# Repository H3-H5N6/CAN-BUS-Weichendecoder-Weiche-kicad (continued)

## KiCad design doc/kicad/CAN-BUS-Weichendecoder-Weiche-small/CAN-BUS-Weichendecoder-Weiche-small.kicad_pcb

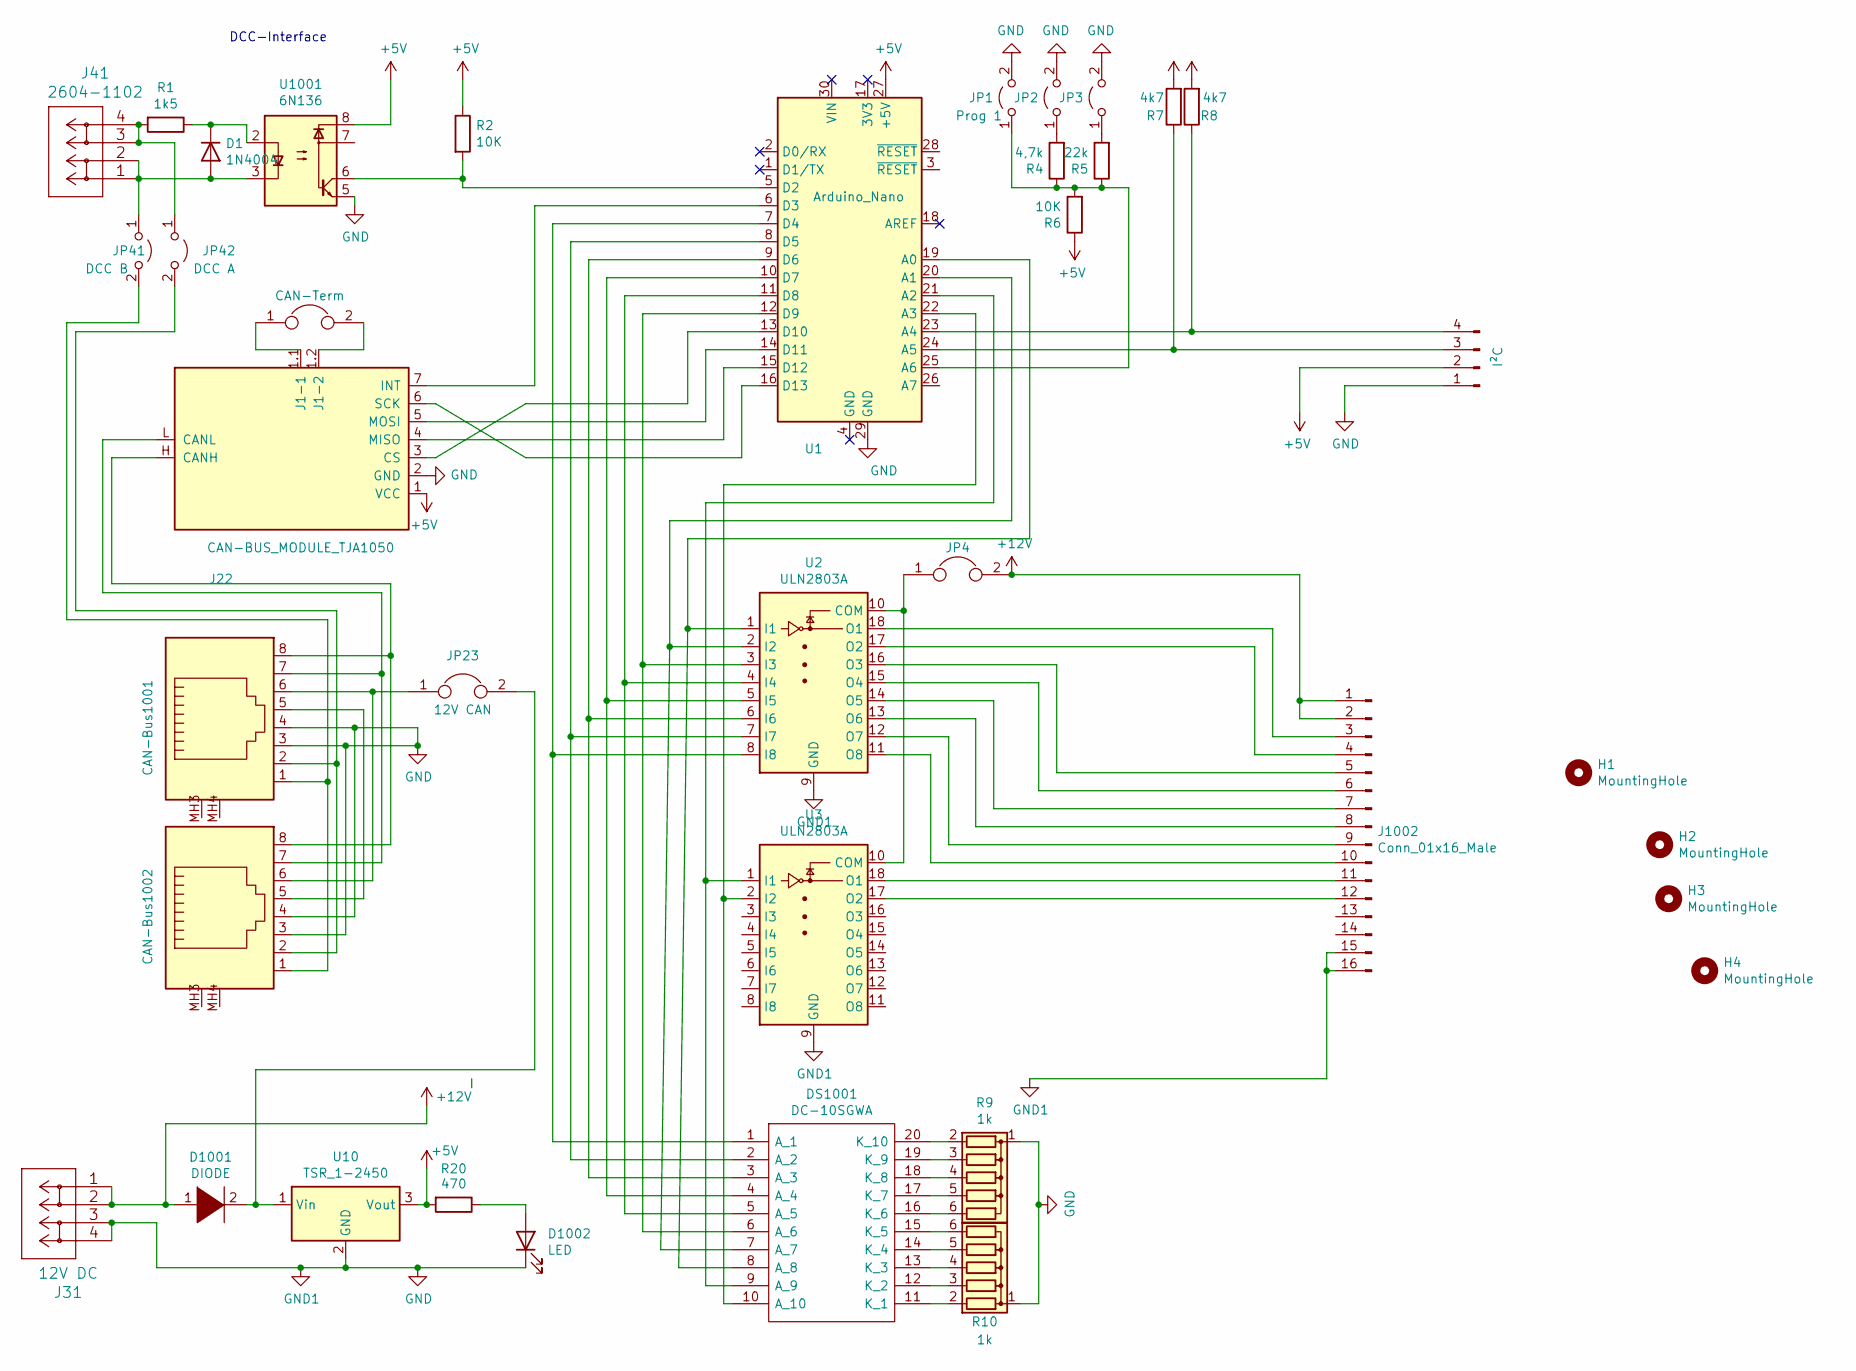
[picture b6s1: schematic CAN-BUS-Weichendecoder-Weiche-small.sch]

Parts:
CAN-Bus1001, CAN-Bus1002: J22; A20042LPFS
D1: 1N4004; D_DO-15_P10.16mm_Horizontal
D1001: DIODE; D_DO-15_P10.16mm_Horizontal
D1002: LED; LED_D3.0mm
DS1001: DC-10SGWA; DIPS750W80P254L2540H825Q20N; Manufacturer_Part_Number DC-10SGWA; Mouser Part Number N/A
H1, H2, H3, H4: MountingHole; MountingHole_3.2mm_M3
J31: 12V DC; CONN_2604-1102_4_WAG
J41: 2604-1102; CONN_2604-1102_4_WAG
J1001: I²C; Pin_Header_Straight_1x04_Pitch2.54mm
J1002: Conn_01x16_Male; SL-116-X-XX_1x16
JP1: Prog 1; Pin_Header_Straight_1x02_Pitch2.54mm
JP2: Prog2; Pin_Header_Straight_1x02_Pitch2.54mm
JP3: Prog3; Pin_Header_Straight_1x02_Pitch2.54mm
JP4: Jumper; Pin_Header_Straight_1x02_Pitch2.54mm
JP11: CAN-Term; Pin_Header_Straight_1x02_Pitch2.54mm
JP23: 12V CAN; Pin_Header_Straight_1x02_Pitch2.54mm
JP41: DCC B; Pin_Header_Straight_1x02_Pitch2.54mm
JP42: DCC A; Pin_Header_Straight_1x02_Pitch2.54mm
R1: 1k5; R_Axial_DIN0207_L6.3mm_D2.5mm_P7.62mm_Horizontal
R2, R6: 10K; R_Axial_DIN0207_L6.3mm_D2.5mm_P7.62mm_Horizontal
R4: 4,7k; R_Axial_DIN0207_L6.3mm_D2.5mm_P7.62mm_Horizontal
R5: 22k; R_Axial_DIN0207_L6.3mm_D2.5mm_P7.62mm_Horizontal
R7, R8: 4k7; R_Axial_DIN0207_L6.3mm_D2.5mm_P7.62mm_Horizontal
R9, R10: 1k; R_Array_SIP6
R20: 470; R_Axial_DIN0207_L6.3mm_D2.5mm_P7.62mm_Horizontal
Shield1001: CAN-BUS_MODULE_TJA1050; MCP2515_CAN_MODULE_BY0-10
U1: Arduino_Nano
U2, U3: ULN2803A; DIP-18_W7.62mm
U10: TSR_1-2450; DCDC-Conv_TRACO_TSR-1
U1001: 6N136; DIP-8_W7.62mm

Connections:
+5V: J1001.2, R2.1, R6.1, R7.2, R8.2, R20.2, Shield1001.1 (VCC), U1.27 (+5V), U10.3 (Vout), U1001.8
+12V: D1001.1 (K), J31.1, J31.2, J1002.1, J1002.2, JP4.2
GND: CAN-Bus1001.3, CAN-Bus1001.4, CAN-Bus1002.3, CAN-Bus1002.4, D1002.1 (K), J31.3, J31.4, J1001.1, J1002.15, J1002.16, JP1.2 (B), JP2.2 (B), JP3.2 (B), R9.1 (common), R10.1 (common), Shield1001.2 (GND), U1.29 (GND), U2.9 (GND), U3.9 (GND), U10.2 (GND), U1001.5
unnamed: CAN-Bus1001.1, CAN-Bus1002.1, JP41.2 (B)
unnamed: CAN-Bus1001.2, CAN-Bus1002.2, JP42.2 (B)
unnamed: CAN-Bus1001.5, CAN-Bus1002.5
unnamed: CAN-Bus1001.6, CAN-Bus1002.6, JP23.1
unnamed: CAN-Bus1001.7, CAN-Bus1002.7, Shield1001.L (CANL)
unnamed: CAN-Bus1001.8, CAN-Bus1002.8, Shield1001.H (CANH)
unnamed: D1.1 (K), R1.1, U1001.2
unnamed: D1.2 (A), J41.1, J41.2, JP41.1 (A), U1001.3
unnamed: D1001.2 (A), JP23.2, U10.1 (Vin)
unnamed: D1002.2 (A), R20.1
unnamed: DS1001.1 (A_1), U1.7 (D4), U2.8 (I8)
unnamed: DS1001.2 (A_2), U1.8 (D5), U2.7 (I7)
unnamed: DS1001.3 (A_3), U1.9 (D6), U2.6 (I6)
unnamed: DS1001.4 (A_4), U1.10 (D7), U2.5 (I5)
unnamed: DS1001.5 (A_5), U1.11 (D8), U2.4 (I4)
unnamed: DS1001.6 (A_6), U1.12 (D9), U2.3 (I3)
unnamed: DS1001.7 (A_7), U1.20 (A1), U2.2 (I2)
unnamed: DS1001.8 (A_8), U1.19 (A0), U2.1 (I1)
unnamed: DS1001.9 (A_9), U1.21 (A2), U3.1 (I1)
unnamed: DS1001.10 (A_10), U1.22 (A3), U3.2 (I2)
unnamed: DS1001.11 (K_1), R10.2 (R1)
unnamed: DS1001.12 (K_2), R10.3 (R2)
unnamed: DS1001.13 (K_3), R10.4 (R3)
unnamed: DS1001.14 (K_4), R10.5 (R4)
unnamed: DS1001.15 (K_5), R10.6 (R5)
unnamed: DS1001.16 (K_6), R9.6 (R5)
unnamed: DS1001.17 (K_7), R9.5 (R4)
unnamed: DS1001.18 (K_8), R9.4 (R3)
unnamed: DS1001.19 (K_9), R9.3 (R2)
unnamed: DS1001.20 (K_10), R9.2 (R1)
unnamed: J41.3, J41.4, JP42.1 (A), R1.2
unnamed: J1001.3, R7.1, U1.24 (A5)
unnamed: J1001.4, R8.1, U1.23 (A4)
unnamed: J1002.3, U2.18 (O1)
unnamed: J1002.4, U2.17 (O2)
unnamed: J1002.5, U2.16 (O3)
unnamed: J1002.6, U2.15 (O4)
unnamed: J1002.7, U2.14 (O5)
unnamed: J1002.8, U2.13 (O6)
unnamed: J1002.9, U2.12 (O7)
unnamed: J1002.10, U2.11 (O8)
unnamed: J1002.11, U3.18 (O1)
unnamed: J1002.12, U3.17 (O2)
unnamed: JP1.1 (A), R4.1, R5.1, R6.2, U1.25 (A6)
unnamed: JP2.1 (A), R4.2
unnamed: JP3.1 (A), R5.2
unnamed: JP4.1, U2.10 (COM), U3.10 (COM)
unnamed: JP11.1, Shield1001.1.1 (J1-1)
unnamed: JP11.2, Shield1001.1.2 (J1-2)
unnamed: R2.2, U1.5 (D2), U1001.6
unnamed: Shield1001.3 (CS), U1.13 (D10)
unnamed: Shield1001.4 (MISO), U1.15 (D12)
unnamed: Shield1001.5 (MOSI), U1.14 (D11)
unnamed: Shield1001.6 (SCK), U1.16 (D13)
unnamed: Shield1001.7 (INT), U1.6 (D3)

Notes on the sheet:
DCC-Interface

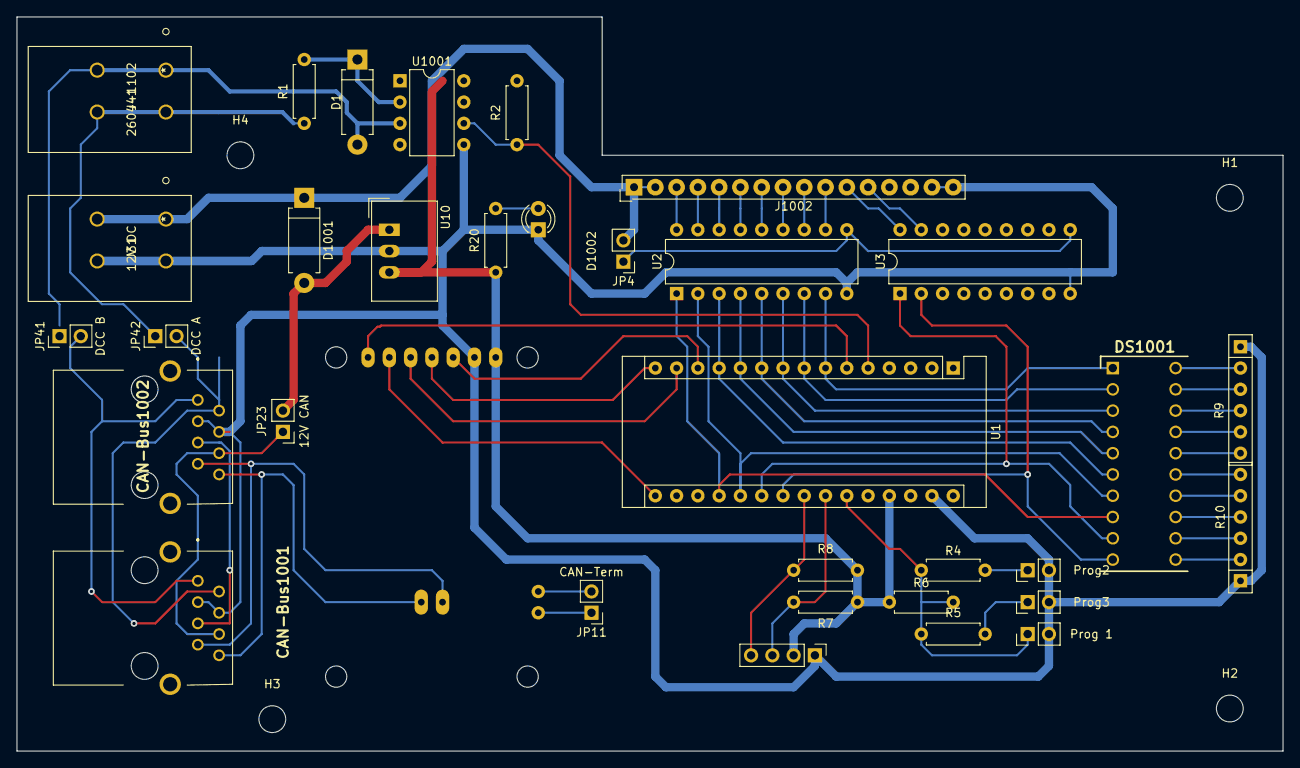
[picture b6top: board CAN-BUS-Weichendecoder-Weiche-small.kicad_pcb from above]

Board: 2 copper layers, 151.1 x 87.6 mm, 38 parts (1 on the bottom side), 58 nets.

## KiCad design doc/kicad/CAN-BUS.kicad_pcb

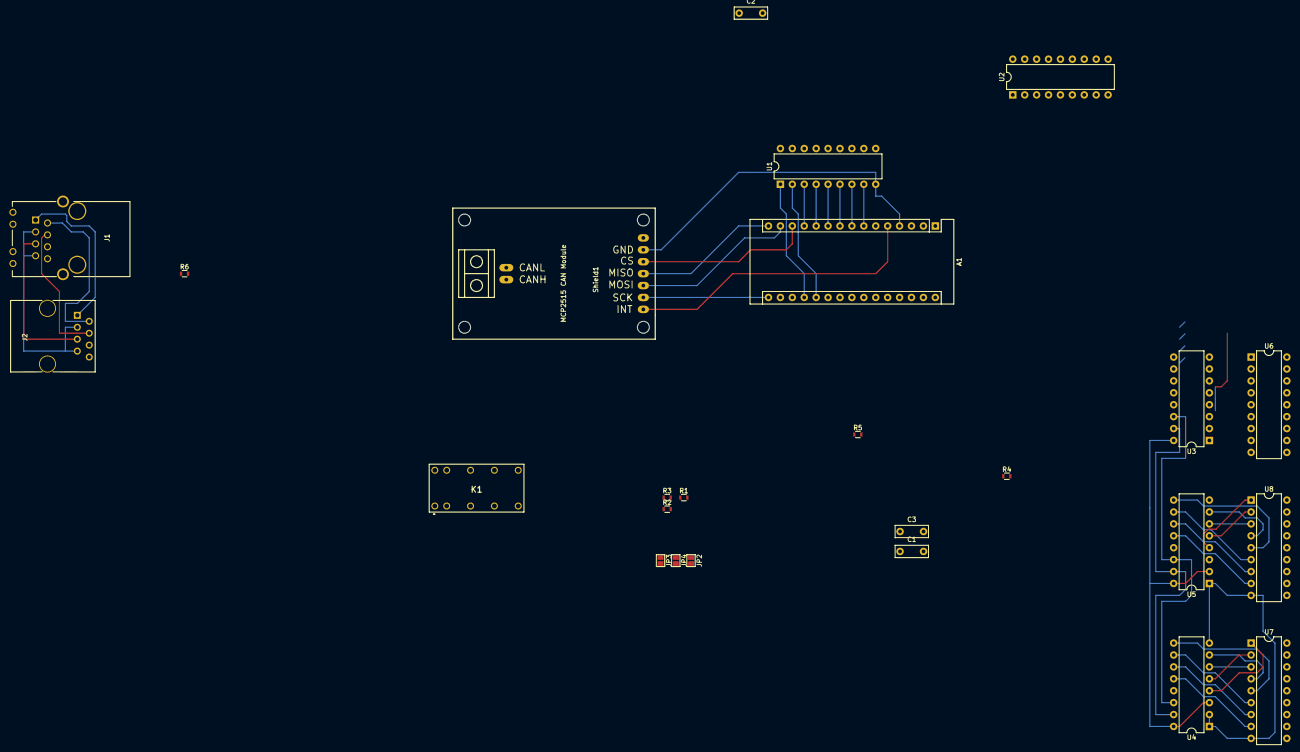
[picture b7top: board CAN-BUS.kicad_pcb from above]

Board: 2 copper layers, 25 parts (0 on the bottom side), 51 nets.

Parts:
A1: Arduino_Nano
C1, C2, C3: 100n; C_Disc_D7.0mm_W2.5mm_P5.00mm
J1: RJ45_LED_Shielded; RJ45_TRANSFO
J2: RJ45_Shielded; RJ45_8
JP2: JP3; GS2
JP3: JP1; GS2
JP4: JP2; GS2
K1: HFD2_005-S-L2-D; HFD2005SL2D
R1: 4,7k; R_0603
R2: 10K; R_0603
R3: 22k; R_0603
R4, R5: 4k7; R_0603
R6: 1K; R_0603
Shield1: CAN-BUS_MODULE_TJA1050; MCP2515_CAN_MODULE_BY0-10
U1, U2, U6, U7, U8: ULN2803A; DIP-18_W7.62mm
U3, U4, U5: PCF8574; DIP-16_W7.62mm

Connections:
+5V: A1.27, C1.1, C2.1, C3.1, J1.8, J2.8, R2.1, R4.2, R5.2, R6.2, Shield1.1, U3.16, U4.3, U4.16, U5.2, U5.16
GND: A1.4, A1.29, C1.2, C2.2, C3.2, J1.3, J1.7, J2.3, J2.7, JP2.2, JP3.2, JP4.2, Shield1.2, U1.9, U2.9, U3.1, U3.2, U3.3, U3.8, U4.1, U4.2, U4.8, U5.1, U5.3, U5.8, U6.9, U7.9, U8.9
unnamed: A1.5, Shield1.7
unnamed: A1.7, U1.8
unnamed: A1.8, U1.7
unnamed: A1.9, U1.6
unnamed: A1.10, U1.5
unnamed: A1.11, U1.4
unnamed: A1.12, U1.3
unnamed: A1.13, Shield1.3
unnamed: A1.14, Shield1.5
unnamed: A1.15, Shield1.4
unnamed: A1.16, Shield1.6
unnamed: A1.19, U1.1
unnamed: A1.20, U1.2
unnamed: A1.21, U2.1
unnamed: A1.22, U2.2
unnamed: A1.23, R5.1, U3.15, U4.15, U5.15
unnamed: A1.24, R4.1, U3.14, U4.14, U5.14
unnamed: A1.25, JP2.1, R1.1, R2.2, R3.1
unnamed: J1.1, J2.1, Shield1.H
unnamed: J1.2, J2.2, Shield1.L
unnamed: J1.4, J2.4
unnamed: J1.5, J2.5
unnamed: J1.6, J2.6
unnamed: JP3.1, R1.2
unnamed: JP4.1, R3.2
unnamed: U3.4, U6.1
unnamed: U3.5, U6.2
unnamed: U3.6, U6.3
unnamed: U3.7, U6.4
unnamed: U3.9, U6.5
unnamed: U3.10, U6.6
unnamed: U3.11, U6.7
unnamed: U3.12, U6.8
unnamed: U4.4, U7.1
unnamed: U4.5, U7.2
unnamed: U4.6, U7.3
unnamed: U4.7, U7.4
unnamed: U4.9, U7.5
unnamed: U4.10, U7.6
unnamed: U4.11, U7.7
unnamed: U4.12, U7.8
unnamed: U5.4, U8.1
unnamed: U5.5, U8.2
unnamed: U5.6, U8.3
unnamed: U5.7, U8.4
unnamed: U5.9, U8.5
unnamed: U5.10, U8.6
unnamed: U5.11, U8.7
unnamed: U5.12, U8.8

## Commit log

2021-03-01 Initial
2021-03-13 Output-Klasse hinzugefügt
2021-03-13 USB als default
2021-03-13 impule implemntiert
2021-03-13 Code formartiert
2021-03-13 Refactoring
2021-03-13 Code formatiert
2021-03-14 Erste CAN-Bus-Anbindung via Loop
2021-03-15 Initial: Tasten der Znetrale auswerten
2021-03-16 Alle 10 LED eingebunden
2021-03-16 Ausgänge als Array
2021-03-16 Array ohne default-Konstructor via malloc anlegen
2021-03-17 Blinken aus/einschalten
2021-03-18 Methode bei Impulse hinzugefügt, mit der man noch eine Nachlaufzeit hat
2021-03-18 LED via Weiche schalten
2021-03-19 Weichen nur stellen, wenn nichts läuft
2021-03-19 Senden von Versionen implemntiert
2021-03-21 Fix Namen
2021-03-21 Farbe und Pinlänge geändert
2021-03-22 Beschreibung hinzugefügt
2021-03-22 Hinweis der Codeanalyse umgesetzt
2021-03-22 Schaltplan angepasst
2021-03-22 CAN-BUS-Modul hinzugefügt
2021-03-22 Schaltung erweitert
2021-03-22 Protokoll-Doku erweitert
2021-03-23 Bedeutung des MSB geändert
2021-03-23 defines für den Zugreiff eingeführt
2021-03-23 Type behoben
2021-03-23 Aktualisiert
2021-04-18 Dateien umbenannt
2021-04-19 Bildgröße verkleinert
2021-04-20 Unbenutzte Libs entfernt
2021-04-20 debug Frame hinzugefügt
2021-04-20 Tastencode geändert
2021-04-20 erweitert
2021-04-22 I2C erste einbindung
2021-04-22 weitere Weichensimulator-Bauteile hinzugefügt
2021-04-22 Alles mal commitet
2021-04-22 Mapping Nummer zu index/pin
2021-04-22 Zugriff auf Expander via Klasse
2021-04-22 Code formatiert, checkAll() hinzugefügt
2021-04-23 Erste implemntierung, um Signalbilder vie i2c ausgeben
2021-04-23 Platine für Adapter 2x3 zu 1x6 hinzugefügt
2021-04-23 Code an Belegung des Steckers angepasst
2021-04-23 Offset für weitere Signale beachten
2021-04-24 Kosmetik
2021-04-24 Debug-Code bei define ausblendbar
2021-04-25 Kosmetik und mehr debug ausblenden
2021-05-04 Ecken rund gemacht, alle mit Montagelöcher
2021-05-06 Platinen, die an jlcpcb geschickt worden sind.
2021-05-06 Aktueller Stand
2021-05-06 Dateien gelöscht/umbeannt
2021-05-06 Dateien, die an jlcpcb geliefert worden sind
2021-05-06 Datei verschoben/umbenannt
2021-05-06 Script zum Erzeugen zip-Files hinzugefügt.
2021-05-06 Datei, die an jlcpcb geliefert worden ist
2021-05-06 Refactoring, 3. I2C hinzugefügt
2021-05-19 Aktuellen Stand gesichert
2021-05-21 v2.0 hinzugefügt
2021-05-21 2. Umschalter herausgeführt
2021-06-22 Programm-Doku hinzugefügt
2021-06-22 Doxygen-Decok hinzugefügt
2021-06-29 Blockschaltbild geändert
2021-06-29 Version 2, jetzt korrekt und auch nutzbar für links, 2. Umschalter herausgeführt
2021-06-29 Bezeichung auf der Bestückungsseite
2021-06-29 Bezeichnung nun auf der Besrückungsseite
2021-06-29 beschreibung auf Bestückungssete, 90°-Kurven durch 45° erstetzt
2021-06-29 Werte der Widerstände hinzugefügt
2021-06-29 Platine weiterentwickelt, aktueller Arbeitsstand
2021-07-13 Doku angepasst
2021-07-25 Doc erweitert.
2021-07-25 gerade/abtweig gibt jetzt immer etwas zurück
2021-08-23 Refactoring: Trennung von Config und State
2021-08-23 Simple Code
2021-08-23 Alle 5 Weichen schalten
2021-08-23 Weichen-Objekt benutzten
2021-08-24 Code aufgeräumt
2021-08-24 2. default vorgesehen
2021-08-29 Weichen können jetzt per Can-Bus geschaltet werden.
2021-08-29 Code aufgeräumt und String via F() ausgeben
2021-08-30 Adresse per Little Endian
2021-08-30 pro can-Frage können jetzt bis zu vier Aktionen durchgeführt werden
2021-08-30 Auf 999 werden die Stände der Weichen gesendet, Code aufgeräumt
2021-08-31 Zweiter Einstellungsblock per id 201
2021-08-31 send Weichenstatus komakter; Code formatiert
2021-08-31 Delay im Lopp verkurzt, damit Can-Bus-Packete schneller verarbeitet werden können
2021-08-31 Senden Status jetzt kompakter
2021-10-01 CAN-IDs aus EEPROM lesen
2021-10-01 Auch die Bedruckung jetzt auf beiden Seiten, Platine jetzt komplett für Links und Rechts
2021-10-03 Active Low/Hight anpepasst an ULN2803
2021-10-03 Konfiguration via Serieller Schnittstelle möglich
2021-10-03 CanConfig über Serial-Schnittstelle extrahiert
2021-10-03 Doppeltes printConfig entfernt
2021-10-05 Wago-Klemmen 250-140x verwendet
2021-10-06 PCP weiterentwickelt
2021-10-06 Beschriftung für A und G korrigiert, Bauteil-Betruckung auf beiden Seiten
2021-10-06 Speicherverbrauch
2021-10-08 Detailierten Weichenstatus wird nun gesendet.
2021-10-09 Erster kompletter Entwurf der Platine
2021-10-10 +5 analog zu GND verlegt
2021-10-11 Status wird immer mit der gleichen ID gesendet
2021-10-11 Beschreibung der CAN-BUS-Frames hinzugefügt
2021-10-11 verbessert
2021-10-19 Aufgeteilt auf zwei Platinen
2021-10-24 ID wieder auf 1 gesetzt (damit die Konfig nicht geändert wird), nur auf die ID 100 und 200 reagieren
2021-10-27 Aktuellen zwischenstand gesichert
2021-10-28 Buchen und Stecker vertauscht und Anordnung kompakter
2021-10-28 Fahrstraßen erweitert
2021-10-28 Docu angepasst
2021-11-05 Anordnung der Bauteile kompakter, 2 statt 3 prog-Pins, nur eine Verbindung zur Weiche
2021-11-06 CAN-Bus-Belegun geändert
2021-11-16 Prog-Eingang einlesen
2021-11-16 DCC POC
2021-11-17 Config-Spreicher für CAN verschoben, DCC notifyChange eingeführt
2021-11-17 DCC-Code extrahiert, Mapping DCC->CAN, Weichen schalten
2021-11-17 Buchen zu den Weichen gedreht, damit sie besser auf das Board passsen
2021-11-19 Letzte Adresse wird immer übernommen, ggf. zeitlich versetzt
2021-11-22 CAN-BUS-Offset überall beachten
2021-11-22 Analog-Pin zur Steuerung der Default-Konfiguration auswerten
2021-11-22 Hilfe ausgeben
2021-11-22 Modul-Id nur #ndern, wenn beide Prog-Jumper gesetzt sind, Can-Bus-Adresse wird mit der Mudul-Id ermittelt
2021-11-23 Weichen auch per Console stellbar
2021-11-25 An der Console die Weichen mit + und - durchschalten
2021-11-25 Mapping Vlaue -> Nummer klappt jetzt korrekt, Datentyp passt nun
2021-11-26 Bilder mit Text hinzugefügt
2022-01-01 Aufgeräumt
2022-01-01 Alte Dateien entfernt
2022-01-01 Alte Datei gelöscht, 6er-Dateien hinzugefügt
2022-01-01 Backup-Dateien entfernt
2022-01-01 Dateien aufgeräumt
2022-01-01 Dateien augeräumt
2022-01-01 Backup-Dateien aus repo entfernt
2022-01-02 Alte Dateien gelöscht
2022-02-17 RJ12 hinzugefügt
2022-02-19 Ausgänge in zwei Blöcke aufgetreilt, Ausgangsspannung kann extern eingespeist werden
2022-02-20 Befsetigungsleucher plaziert
2022-02-20 Beschriftung hinzugefügt
2022-02-20 Beschriftung bearbeit und Bemaßung erweitert
2022-02-20 Flächen gefült und DRC-Warnung beseitigt
2022-02-21 Lage der Stecker angepasst
2022-02-21 i2c-Adresse bewchriftet, RJ12 neu ausgerichtet
2022-02-21 Version auf 1.1 geändert + Kosmetik
2022-04-01 Belegmelder verschoben in ein eignes Projekt
2022-04-01 Widerständer auf Rückseite, Widerstandswerte angepasst
2022-04-01 Pullup-Widerstand hinzugefügt; Power-LED hinzugefügt
2022-04-01 Altes Backup entfernt
2022-04-05 Signalsimulator RJ12 hinzugefügt
2022-04-05 Reihenfolge der Libs haben sich geändert
2022-04-05 Einstellungen geändert
2022-04-05 Backup-Files ausgeschlosen
2022-04-12 Init i2c hinzugefügt
2022-04-12 Docu erweitert
2022-04-12 i2c adresse spreichern
2022-04-12 I2C in eine Klasse verschoben
2022-04-13 PCF initialisieren und HP0 ausgeben, speicherverbrauch ausgeben.
2022-04-14 Mehr String mit F-Macro gespeichert, Liste der i2c-Adressen nac I2C-Tools.h verschoben
2022-04-14 Ports per Schleife initialisieren
2022-04-15 ConfigPin in Klasse ausgelagert
2022-04-15 Debug-Zeile angepasst
2022-04-15 Weitere Strings in f-Makro gepackt
2022-04-15 DCC -Adresse bei der Konfig ausgeben; Prefix bei der Config ausgeben
2022-04-18 Erste Implementierung Ausgabe Signal via i2c
2022-04-18 Enums sind jetzt uint8_t statt int
2022-04-18 Unterschiedliche Steckerbelegungen werden unterstützt; Belegung der Ausgänge beachtet
2022-04-19 Compile-Warnung beseitigt
2022-04-19 Belegung der Stecker anhepasst
2022-04-19 Widerstandswerte angepasst
2022-04-28 CAN-Code in extra-Klasse ausgelagert
2022-04-28 Can-Steuerung komplett ausgelageert.
2022-04-28 canConfig per Pointer übergeben und Code formatiert
2022-04-28 Pins via definie definiert, unbenutzte Variable entfernt
2022-05-02 DCCtoCAN als Methode und Kommentar hinzugefügt
2022-05-02 CanConfig schreiben gegliedert
2022-05-02 Adressen jetzt bei der Weiche selbst hinterlegen
2022-05-03 CAN-Konfiguration umgebaut
2022-05-06 Debug verbessert, statusForCan beschrieben
2022-05-06 Daten für Weichenstatus ist in einem 2x4-Array
2022-05-06 Debug verbessert
2022-05-06 change bur Aufrufen, wenn due Adresse passt. Verbesssert die Reihenfolge der Debug-Meldungen
2022-05-06 nextAddress nur übernehmen, wenn sie neu ist
2022-05-06 Beschreibung erweitert
2022-05-06 Signal hat jetzt auch die Methode find
2022-05-07 Methode umbenannt
2022-05-07 Hilfe erweitert
2022-05-07 Siganl und Weichen werden jetzt Seriel unabhänig gestellt
2022-05-08 Mapping DCC -> CAN hinzugefügt
2022-05-08 DCC debounce hinzugefügt
2022-05-08 Callback immer im Konstruktor übergeben
2022-05-08 DCC-Debounce für Weichen und Signale hinzugefügt
2022-05-08 Dcc-Debounce via Basisklasse (für Weiche)
2022-05-08 Dcc-Debounce via Basisklasse (für Signal)
2022-05-09 Default-Konstruktor hinzugefügt
2022-05-09 getDebounceMask jetzt virtuell, debounceBits initialisiert
2022-05-09 Default-Konstruktor hinzugefügt, Code aufgeräumt
2022-05-09 Default-Konstruktor hinzugefügt, Code aufgeräumt, Varibalen initialisiert
2022-05-09 Varibalen initialisiert, Hilfe und CLI kann via define deaktiviert werden, wenn der Speicher mal knapp wird.
2022-05-09 Arrays mit Weiche und Signal via Default-Konstrutor initialiseren
2022-05-09 Default-Konstruktor hinzugefügt, viruelle Methode implementiert, alle Member initialisert
2022-05-09 Testcode entfernt
2022-05-09 Array mit mem... löschen bzw. kopieren
2022-05-09 neues env ...Debug hinzugefügt, flags für inspect hinzugefügt
2022-05-09 Alte Deteien gelöscht
2022-05-09 DCC etwas speicherärmer auf die CAN-Adresse mappen
2023-11-30 Kicad-Dateien in Wurzel verschoben
